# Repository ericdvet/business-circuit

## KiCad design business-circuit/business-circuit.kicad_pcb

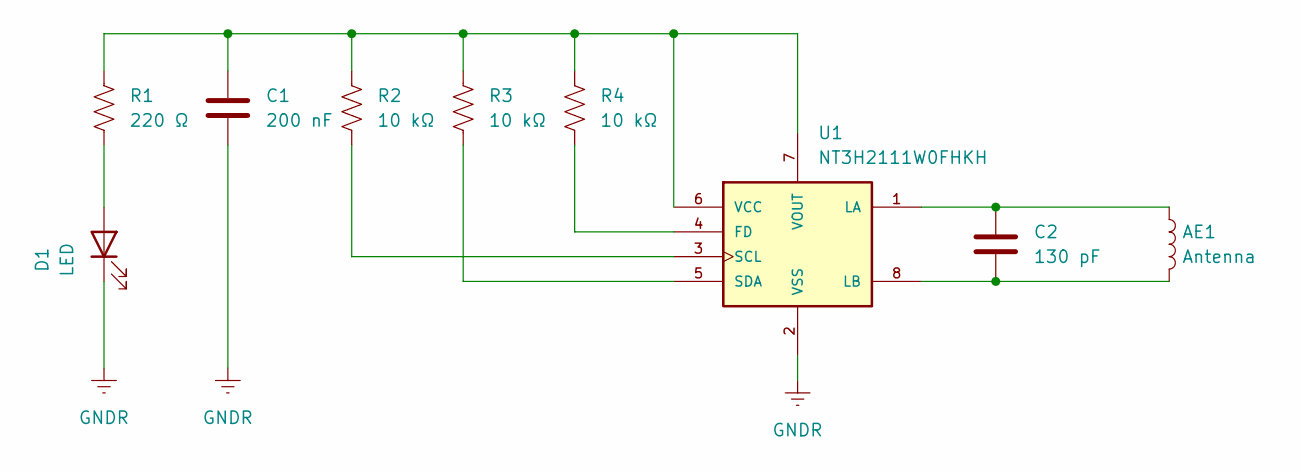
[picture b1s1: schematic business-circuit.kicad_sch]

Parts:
AE1: Antenna; 54X27_3TURNS_THIN
C1: 200 nF; C_0402_1005Metric_Pad0.74x0.62mm_HandSolder
C2: 130 pF; C_0402_1005Metric_Pad0.74x0.62mm_HandSolder
D1: LED; LED_0402_1005Metric
R1: 220 Ω; R_0402_1005Metric_Pad0.72x0.64mm_HandSolder
R2, R3, R4: 10 kΩ; R_0402_1005Metric_Pad0.72x0.64mm_HandSolder
U1: NT3H2111W0FHKH; SOT96-1

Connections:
GNDR: C1.2, D1.1 (K), U1.2 (VSS)
unnamed: D1.2 (A), R1.2
unnamed: R4.2, U1.4 (FD)
unnamed: AE1.1, C2.1, U1.1 (LA)
unnamed: AE1.2, C2.2, U1.8 (LB)
unnamed: R2.2, U1.3 (SCL)
unnamed: R3.2, U1.5 (SDA)
unnamed: C1.1, R1.1, R2.1, R3.1, R4.1, U1.6 (VCC), U1.7 (VOUT)

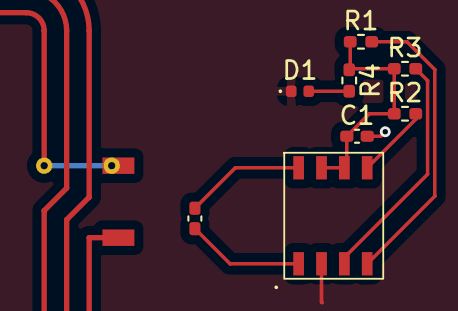
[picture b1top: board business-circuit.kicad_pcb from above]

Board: 2 copper layers, 9 parts (0 on the bottom side), 8 nets.

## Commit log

2025-03-06 schematic done pending clean up
2025-03-14 pre board review
2025-03-14 need to add antenna
2025-03-14 redid schematic with antenna
2025-03-14 pre importing antenna
2025-03-14 antenna broke SRC :(
